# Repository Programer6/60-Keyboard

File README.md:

# 60%-Keyboard

Design for 60% keyboard with KMK firmware because I wanted a compact, minimal layout that saves space without sacrificing functionality. Full-sized keyboards felt bulky for my setup! This is my first keyboard, which I designed, so I wanted to keep think simple (no QMK, ofc)

# PCB
- The PCB's size is
- 61x key default 60% Layout!
- 2x Rotary Encoder
- 2 screens!

## Images

| Schematic                 |
| ------------------------- |
|  |
|  |

| PCB                   |
| --------------------- |
|  |

| Case                  |
| --------------------- |
|  |
| 
|

## BOM 
| Name | Qty | Final Price | Link |
| :--- | :-- | :---------- | :--- |
| Cherry Profile PBT Keycaps | 1 | 17 | [Link](https://www.aliexpress.com/item/1005009109030179.html) |
| EC11s Rotary Encoder Code 5pin | | 8 | [Link](https://www.aliexpress.us/item/1005008610645902.html) |
| Knob | 2 | 6 |Preint Legend|
| OLED Module 1 | 1 | 4 | [Link](https://www.aliexpress.com/item/1005007038294972.html) |
| OLED Module 2 | 1 | 4 | |
| Gateron EF Grayish | 70 | 22 | Will buy myself [Link](https://www.aliexpress.us/item/1005006358112479.html) |
| Plate Mount Stabilizers | 9 | 9 | [Link](https://www.aliexpress.us/item/1005006528731543.html) |
| m3 16 mm | 10 | 3 | [Link](https://www.aliexpress.us/item/32810872544.html) |
| M3 25 mm | 10 | 3 | [Link](https://www.aliexpress.us/item/32810872544.html) |
| PCB | 44 | 40 | |
| Raspberry Pi Pico | 6 | 6 | [Link](https://www.aliexpress.us/item/1005007661444023.html) |
| Poron Gasket Strip | | 4 | [Link](https://www.aliexpress.com/item/1005003607093794.html) |
| M3(OD4.2mm) Heatset Insert | 25 | 2 | [Link](https://www.aliexpress.us/item/1005003582355741.html) |
| Keyboard Case | 1 | 5 | Print Legend |
| Diode 1N4148 Through | 80 | 1.3 | [Link](https://www.aliexpress.us/item/4000142272546.html) |

## Total Pricing
140$ - High estimate price rounded up! & buffer

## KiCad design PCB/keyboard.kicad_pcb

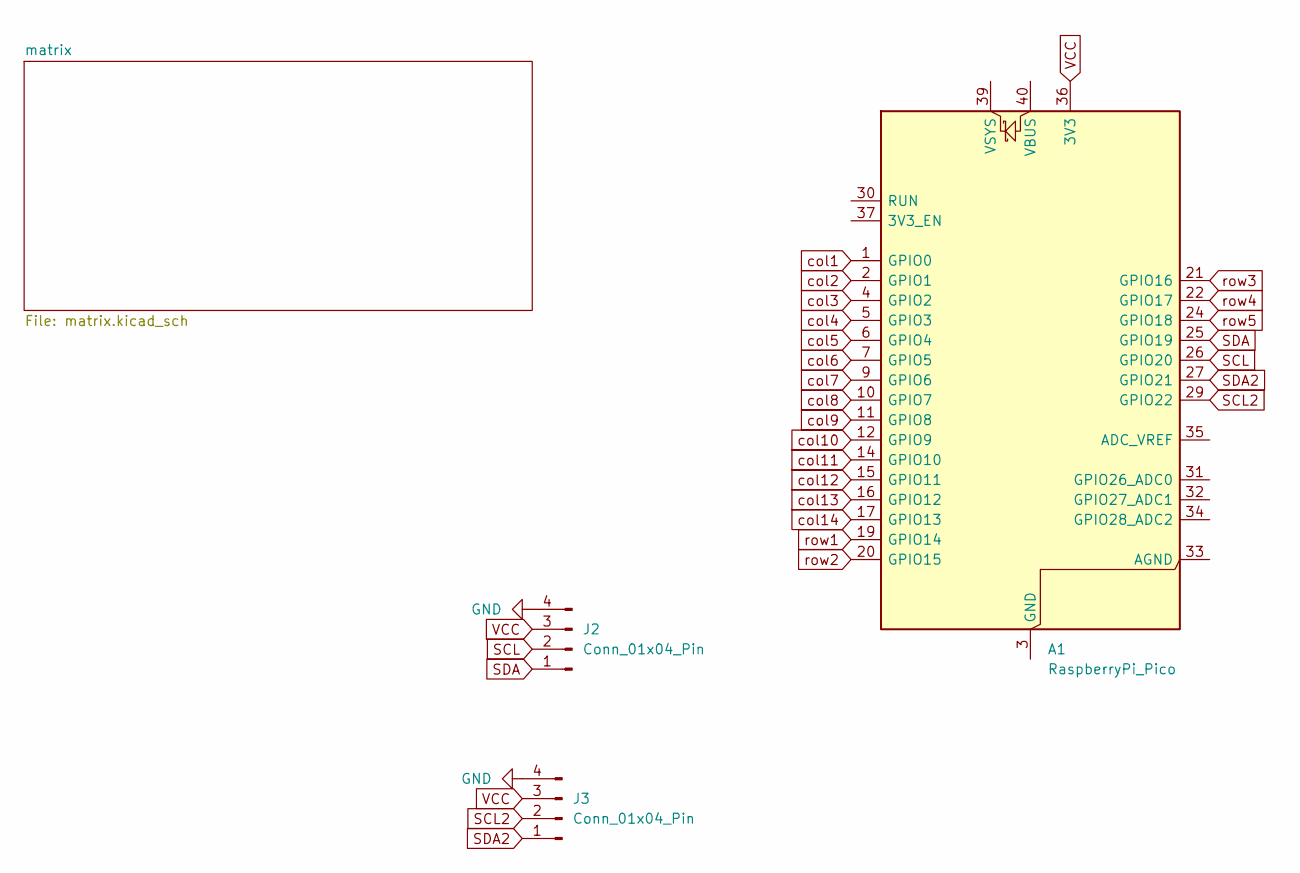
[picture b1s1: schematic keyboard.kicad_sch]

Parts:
A1: RaspberryPi_Pico; RaspberryPi_Pico_Common_Unspecified
J2, J3: Conn_01x04_Pin; SSD1306-0.91-OLED-4pin-128x32

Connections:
GND: J2.4, J3.4; also elsewhere on the board
unnamed: A1.3 (GND), A1.8 (GND), A1.13 (GND), A1.18 (GND), A1.23 (GND), A1.28 (GND), A1.38 (GND)
SCL: A1.26 (GPIO20), J2.2
SCL2: A1.29 (GPIO22), J3.2
SDA: A1.25 (GPIO19), J2.1
SDA2: A1.27 (GPIO21), J3.1
VCC: A1.36 (3V3), J2.3, J3.3
col1: A1.1 (GPIO0); also elsewhere on the board
col2: A1.2 (GPIO1); also elsewhere on the board
col3: A1.4 (GPIO2); also elsewhere on the board
col4: A1.5 (GPIO3); also elsewhere on the board
col5: A1.6 (GPIO4); also elsewhere on the board
col6: A1.7 (GPIO5); also elsewhere on the board
col7: A1.9 (GPIO6); also elsewhere on the board
col8: A1.10 (GPIO7); also elsewhere on the board
col9: A1.11 (GPIO8); also elsewhere on the board
col10: A1.12 (GPIO9); also elsewhere on the board
col11: A1.14 (GPIO10); also elsewhere on the board
col12: A1.15 (GPIO11); also elsewhere on the board
col13: A1.16 (GPIO12); also elsewhere on the board
col14: A1.17 (GPIO13); also elsewhere on the board
row1: A1.19 (GPIO14); also elsewhere on the board
row2: A1.20 (GPIO15); also elsewhere on the board
row3: A1.21 (GPIO16); also elsewhere on the board
row4: A1.22 (GPIO17); also elsewhere on the board
row5: A1.24 (GPIO18); also elsewhere on the board

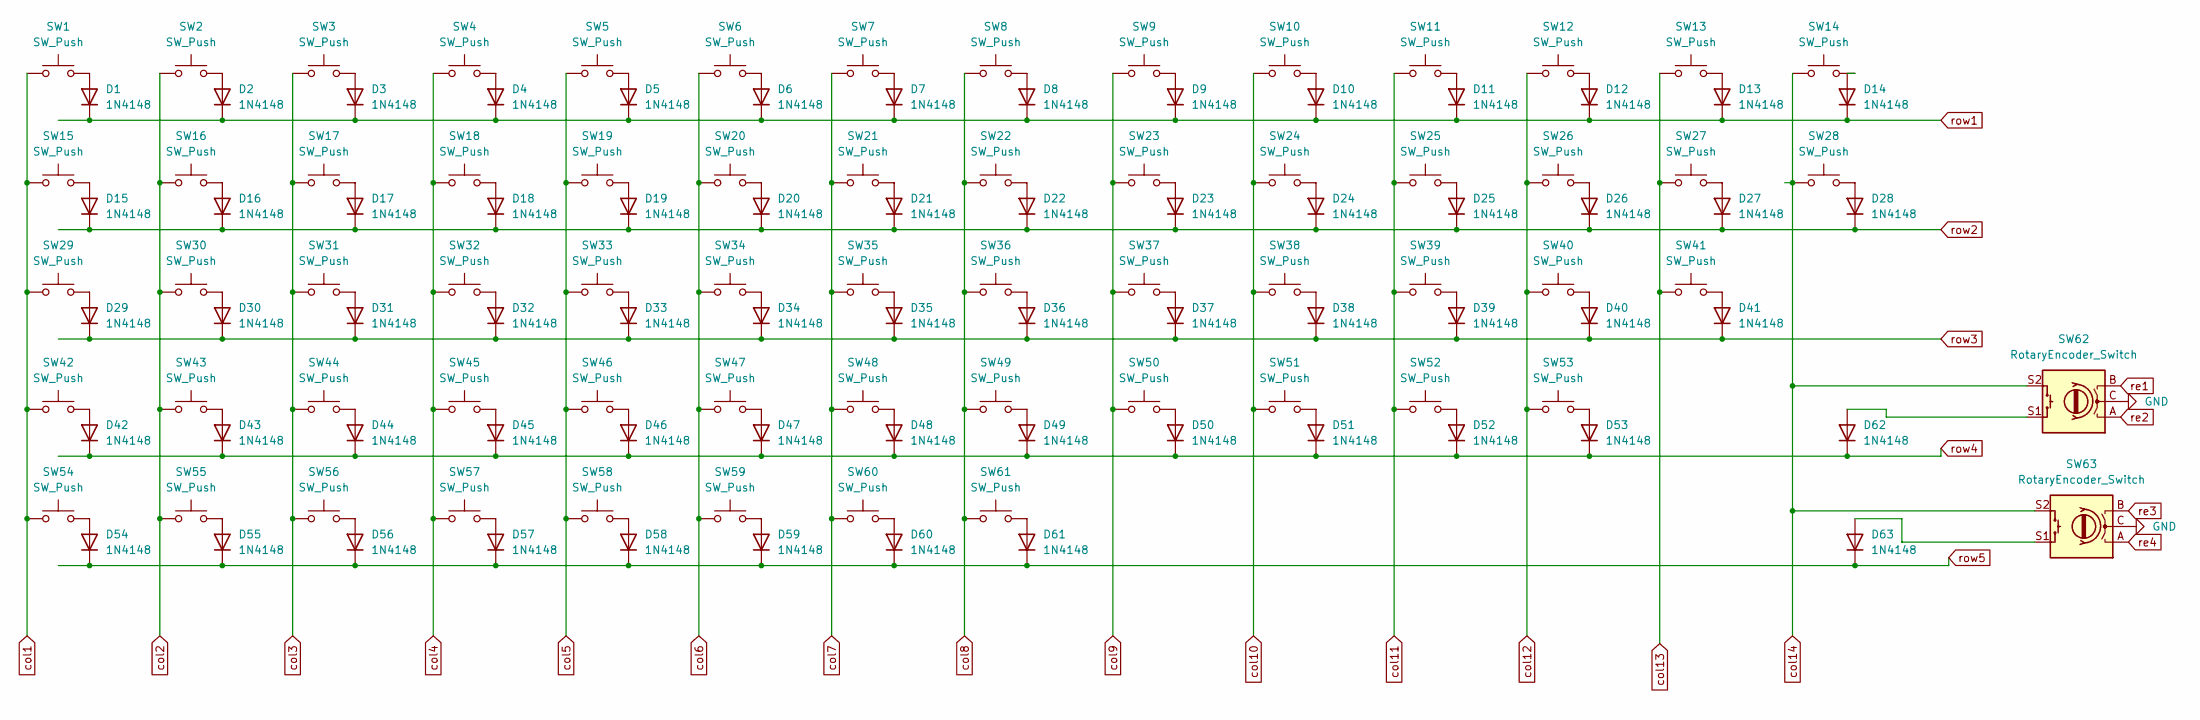
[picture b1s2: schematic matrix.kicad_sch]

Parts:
D1, D2, D3, D4, D5, D6, D7, D8, D9, D10, D11, D12, D13, D14, D15, D16, D17, D18, D19, D20, D21, D22, D23, D24, D25, D26, D27, D28, D29, D30, D31, D32, D33, D34, D35, D36, D37, D38, D39, D40, D41, D42, D43, D44, D45, D46, D47, D48, D49, D50, D51, D52, D53, D54, D55, D56, D57, D58, D59, D60, D61, D62, D63: 1N4148; D_DO-35_SOD27_P7.62mm_Horizontal
SW1, SW2, SW3, SW4, SW5, SW6, SW7, SW8, SW9, SW10, SW11, SW12, SW13, SW16, SW17, SW18, SW19, SW20, SW21, SW22, SW23, SW24, SW25, SW26, SW27, SW30, SW31, SW32, SW33, SW34, SW35, SW36, SW37, SW38, SW39, SW40, SW43, SW44, SW45, SW46, SW47, SW48, SW49, SW50, SW51, SW52: SW_Push; SW_Cherry_MX_1.00u_PCB
SW14: SW_Push; SW_Cherry_MX_2.00u_PCB
SW15, SW28: SW_Push; SW_Cherry_MX_1.50u_PCB
SW29: SW_Push; SW_Cherry_MX_1.75u_PCB
SW41, SW42: SW_Push; SW_Cherry_MX_2.25u_PCB
SW53: SW_Push; SW_Cherry_MX_2.75u_PCB
SW54, SW55, SW56, SW58, SW59, SW60, SW61: SW_Push; SW_Cherry_MX_1.25u_PCB
SW57: SW_Push; SW_Cherry_MX_6.25u_PCB
SW62, SW63: RotaryEncoder_Switch; RotaryEncoder_Alps_EC11E-Switch_Vertical_H20mm_CircularMoun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

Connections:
GND: SW62.C, SW63.C; also elsewhere on the board
unnamed: D1.2 (A), SW1.2
unnamed: D2.2 (A), SW2.2
unnamed: D3.2 (A), SW3.2
unnamed: D4.2 (A), SW4.2
unnamed: D5.2 (A), SW5.2
unnamed: D6.2 (A), SW6.2
unnamed: D7.2 (A), SW7.2
unnamed: D8.2 (A), SW8.2
unnamed: D9.2 (A), SW9.2
unnamed: D10.2 (A), SW10.2
unnamed: D11.2 (A), SW11.2
unnamed: D12.2 (A), SW12.2
unnamed: D13.2 (A), SW13.2
unnamed: D14.2 (A), SW14.2
unnamed: D15.2 (A), SW15.2
unnamed: D16.2 (A), SW16.2
unnamed: D17.2 (A), SW17.2
unnamed: D18.2 (A), SW18.2
unnamed: D19.2 (A), SW19.2
unnamed: D20.2 (A), SW20.2
unnamed: D21.2 (A), SW21.2
unnamed: D22.2 (A), SW22.2
unnamed: D23.2 (A), SW23.2
unnamed: D24.2 (A), SW24.2
unnamed: D25.2 (A), SW25.2
unnamed: D26.2 (A), SW26.2
unnamed: D27.2 (A), SW27.2
unnamed: D28.2 (A), SW28.2
unnamed: D29.2 (A), SW29.2
unnamed: D30.2 (A), SW30.2
unnamed: D31.2 (A), SW31.2
unnamed: D32.2 (A), SW32.2
unnamed: D33.2 (A), SW33.2
unnamed: D34.2 (A), SW34.2
unnamed: D35.2 (A), SW35.2
unnamed: D36.2 (A), SW36.2
unnamed: D37.2 (A), SW37.2
unnamed: D38.2 (A), SW38.2
unnamed: D39.2 (A), SW39.2
unnamed: D40.2 (A), SW40.2
unnamed: D41.2 (A), SW41.2
unnamed: D42.2 (A), SW42.2
unnamed: D43.2 (A), SW43.2
unnamed: D44.2 (A), SW44.2
unnamed: D45.2 (A), SW45.2
unnamed: D46.2 (A), SW46.2
unnamed: D47.2 (A), SW47.2
unnamed: D48.2 (A), SW48.2
unnamed: D49.2 (A), SW49.2
unnamed: D50.2 (A), SW50.2
unnamed: D51.2 (A), SW51.2
unnamed: D52.2 (A), SW52.2
unnamed: D53.2 (A), SW53.2
unnamed: D54.2 (A), SW54.2
unnamed: D55.2 (A), SW55.2
unnamed: D56.2 (A), SW56.2
unnamed: D57.2 (A), SW57.2
unnamed: D58.2 (A), SW58.2
unnamed: D59.2 (A), SW59.2
unnamed: D60.2 (A), SW60.2
unnamed: D61.2 (A), SW61.2
unnamed: D62.2 (A), SW62.S1
unnamed: D63.2 (A), SW63.S1
col1: SW1.1, SW15.1, SW29.1, SW42.1, SW54.1; also elsewhere on the board
col2: SW2.1, SW16.1, SW30.1, SW43.1, SW55.1; also elsewhere on the board
col3: SW3.1, SW17.1, SW31.1, SW44.1, SW56.1; also elsewhere on the board
col4: SW4.1, SW18.1, SW32.1, SW45.1, SW57.1; also elsewhere on the board
col5: SW5.1, SW19.1, SW33.1, SW46.1, SW58.1; also elsewhere on the board
col6: SW6.1, SW20.1, SW34.1, SW47.1, SW59.1; also elsewhere on the board
col7: SW7.1, SW21.1, SW35.1, SW48.1, SW60.1; also elsewhere on the board
col8: SW8.1, SW22.1, SW36.1, SW49.1, SW61.1; also elsewhere on the board
col9: SW9.1, SW23.1, SW37.1, SW50.1; also elsewhere on the board
col10: SW10.1, SW24.1, SW38.1, SW51.1; also elsewhere on the board
col11: SW11.1, SW25.1, SW39.1, SW52.1; also elsewhere on the board
col12: SW12.1, SW26.1, SW40.1, SW53.1; also elsewhere on the board
col13: SW13.1, SW27.1, SW41.1; also elsewhere on the board
col14: SW14.1, SW28.1, SW62.S2, SW63.S2; also elsewhere on the board
re1: SW62.B
re2: SW62.A
re3: SW63.B
re4: SW63.A
row1: D1.1 (K), D2.1 (K), D3.1 (K), D4.1 (K), D5.1 (K), D6.1 (K), D7.1 (K), D8.1 (K), D9.1 (K), D10.1 (K), D11.1 (K), D12.1 (K), D13.1 (K), D14.1 (K); also elsewhere on the board
row2: D15.1 (K), D16.1 (K), D17.1 (K), D18.1 (K), D19.1 (K), D20.1 (K), D21.1 (K), D22.1 (K), D23.1 (K), D24.1 (K), D25.1 (K), D26.1 (K), D27.1 (K), D28.1 (K); also elsewhere on the board
row3: D29.1 (K), D30.1 (K), D31.1 (K), D32.1 (K), D33.1 (K), D34.1 (K), D35.1 (K), D36.1 (K), D37.1 (K), D38.1 (K), D39.1 (K), D40.1 (K), D41.1 (K); also elsewhere on the board
row4: D42.1 (K), D43.1 (K), D44.1 (K), D45.1 (K), D46.1 (K), D47.1 (K), D48.1 (K), D49.1 (K), D50.1 (K), D51.1 (K), D52.1 (K), D53.1 (K), D62.1 (K); also elsewhere on the board
row5: D54.1 (K), D55.1 (K), D56.1 (K), D57.1 (K), D58.1 (K), D59.1 (K), D60.1 (K), D61.1 (K), D63.1 (K); also elsewhere on the board

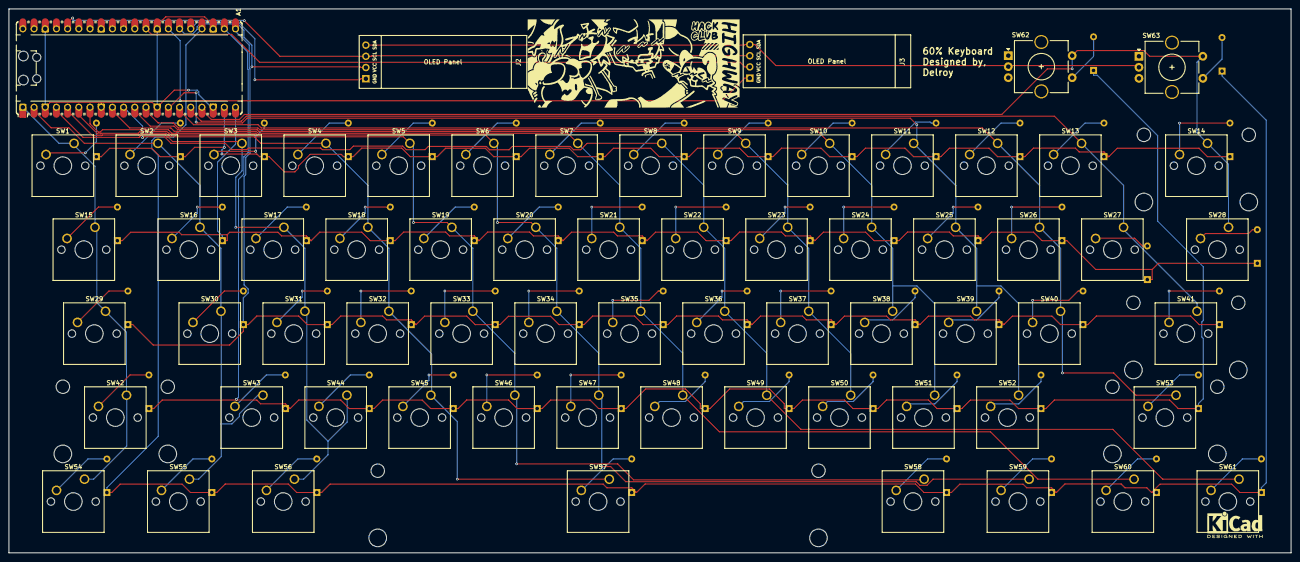
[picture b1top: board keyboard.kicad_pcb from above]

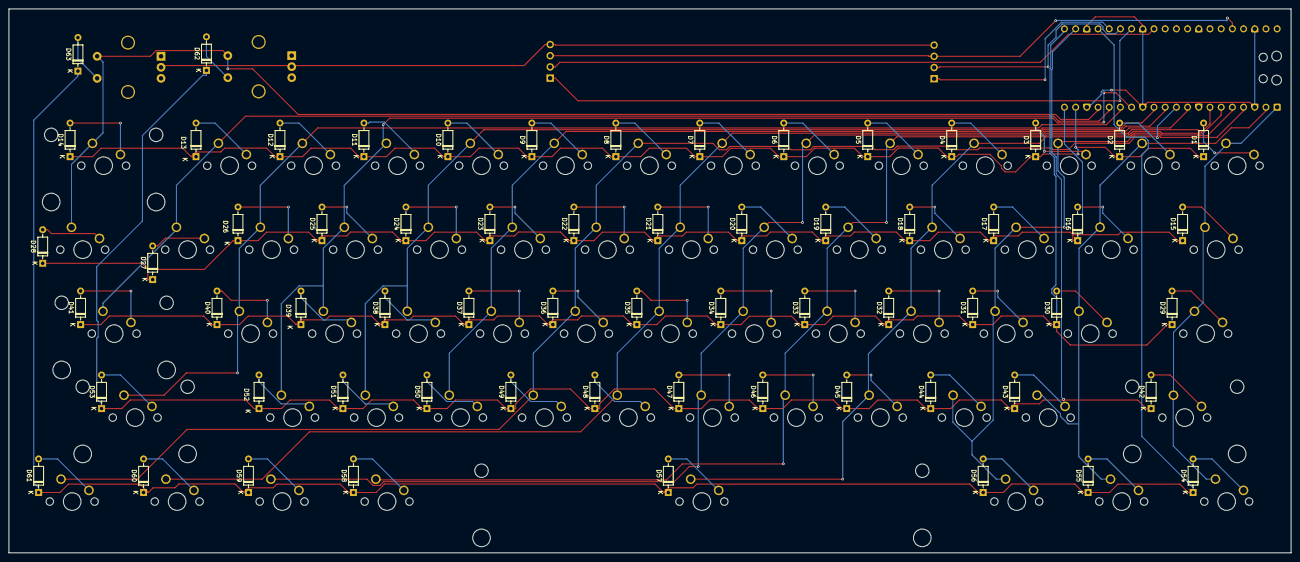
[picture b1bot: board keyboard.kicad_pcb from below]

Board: 2 copper layers, 290.9 x 123.4 mm, 129 parts (63 on the bottom side), 89 nets.

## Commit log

2025-07-19 Create test
2025-07-19 Create production
